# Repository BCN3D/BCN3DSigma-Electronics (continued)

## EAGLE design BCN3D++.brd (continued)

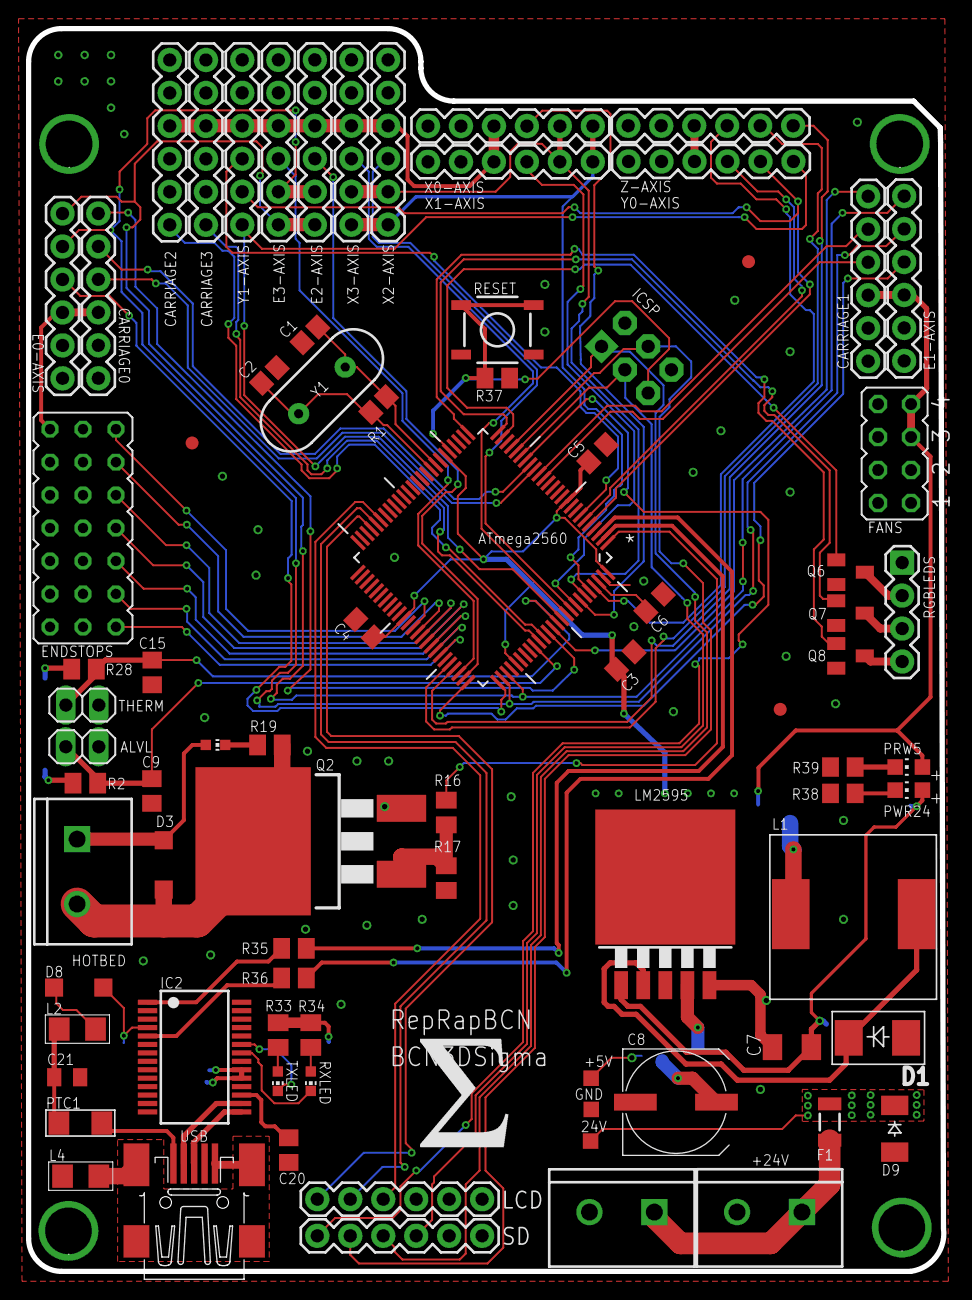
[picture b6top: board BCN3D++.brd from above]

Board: 2 copper layers, 70.5 x 95.8 mm, 87 parts (1 on the bottom side), 79 nets.

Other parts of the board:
U$5: SIGMA_LOGO

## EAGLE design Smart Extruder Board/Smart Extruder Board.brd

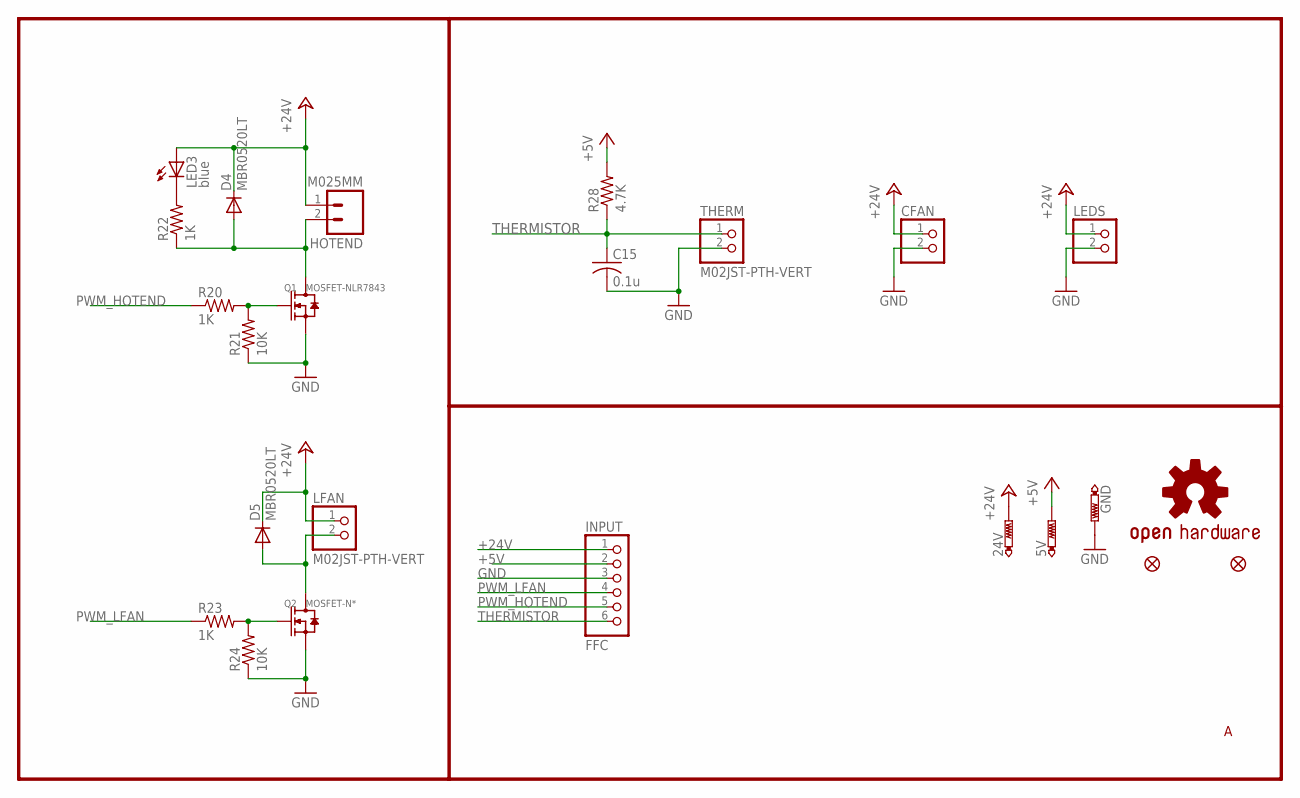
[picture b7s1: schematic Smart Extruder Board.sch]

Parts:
5V, 24V: PTR1TP10SQ; TP10SQ
C15: 0.1u; C0805; MPN 08055C104KAT2A
CFAN: PINHD-1X2/90; 1X02/90
D4, D5: MBR0520LT; SOD123; MPN B0530W-7-F
GND: PTR1TP10SQ; TP10SQ
HOTEND: M025MM; SCREWTERMINAL-5MM-2
INPUT: FFC; 1X06/90
JP1, JP3: SPARKFUN_FIDUCIAL1X2.5; SPARKFUN_FIDUCIAL-1X2.5
LED3: blue; CHIP-LED0805; MPN OVS-0803
LEDS: PINHD-1X2/90; 1X02/90
LFAN: M02JST-PTH-VERT; 1X02/90
LOGO1: OSHW-LOGOS; OSHW-LOGO-S
Q1: MOSFET-NLR7843; TO252; MPN IRLR7843PBF
Q2: MOSFET-N*; SOT23; MPN IRLML6344TRPBF
R20, R22, R23: 1K; M0805; MPN CR0805-JW-102ELF
R21, R24: 10K; M0805; MPN CR0805-JW-103ELF
R28: 4.7K; M0805; MPN CR0805-FX-4701GLF
THERM: M02JST-PTH-VERT; 1X02/90

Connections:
+5V: 5V.TP, INPUT.2, R28.2
+24V: 24V.TP, CFAN.1, D4.C, D5.C, HOTEND.1, INPUT.1, LED3.A, LEDS.1, LFAN.1
GND: C15.2, CFAN.2, GND.TP, INPUT.3, LEDS.2, Q1.2 (S), Q2.2 (S), R21.1, R24.1, THERM.2
unnamed: Q1.1 (G), R20.2, R21.2
unnamed: D4.A, HOTEND.2, Q1.3 (D), R22.1
unnamed: LED3.C, R22.2
unnamed: Q2.1 (G), R23.2, R24.2
unnamed: D5.A, LFAN.2, Q2.3 (D)
PWM_HOTEND: INPUT.5, R20.1
PWM_LFAN: INPUT.4, R23.1
THERMISTOR: C15.1, INPUT.6, R28.1, THERM.1

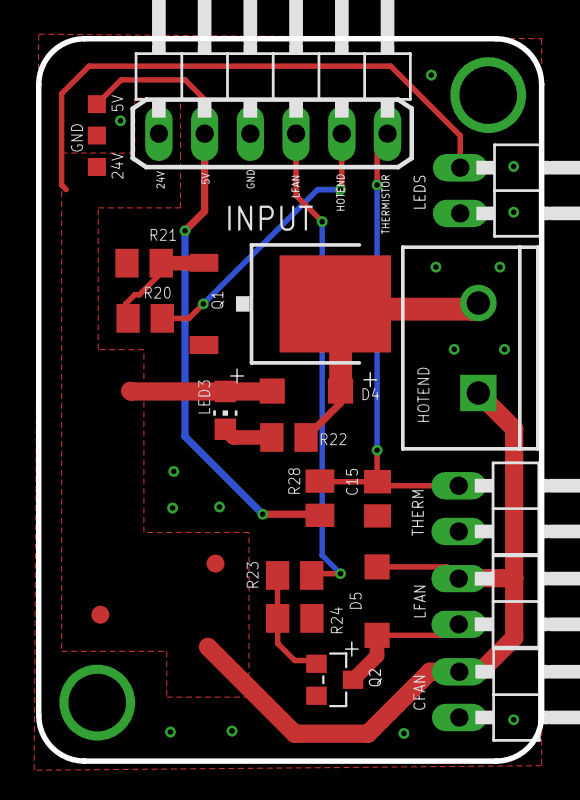
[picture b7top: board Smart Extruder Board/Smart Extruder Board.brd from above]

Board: 2 copper layers, 27.9 x 40.1 mm, 25 parts (1 on the bottom side), 11 nets.

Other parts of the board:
DRILEGEND: DRILEGEND

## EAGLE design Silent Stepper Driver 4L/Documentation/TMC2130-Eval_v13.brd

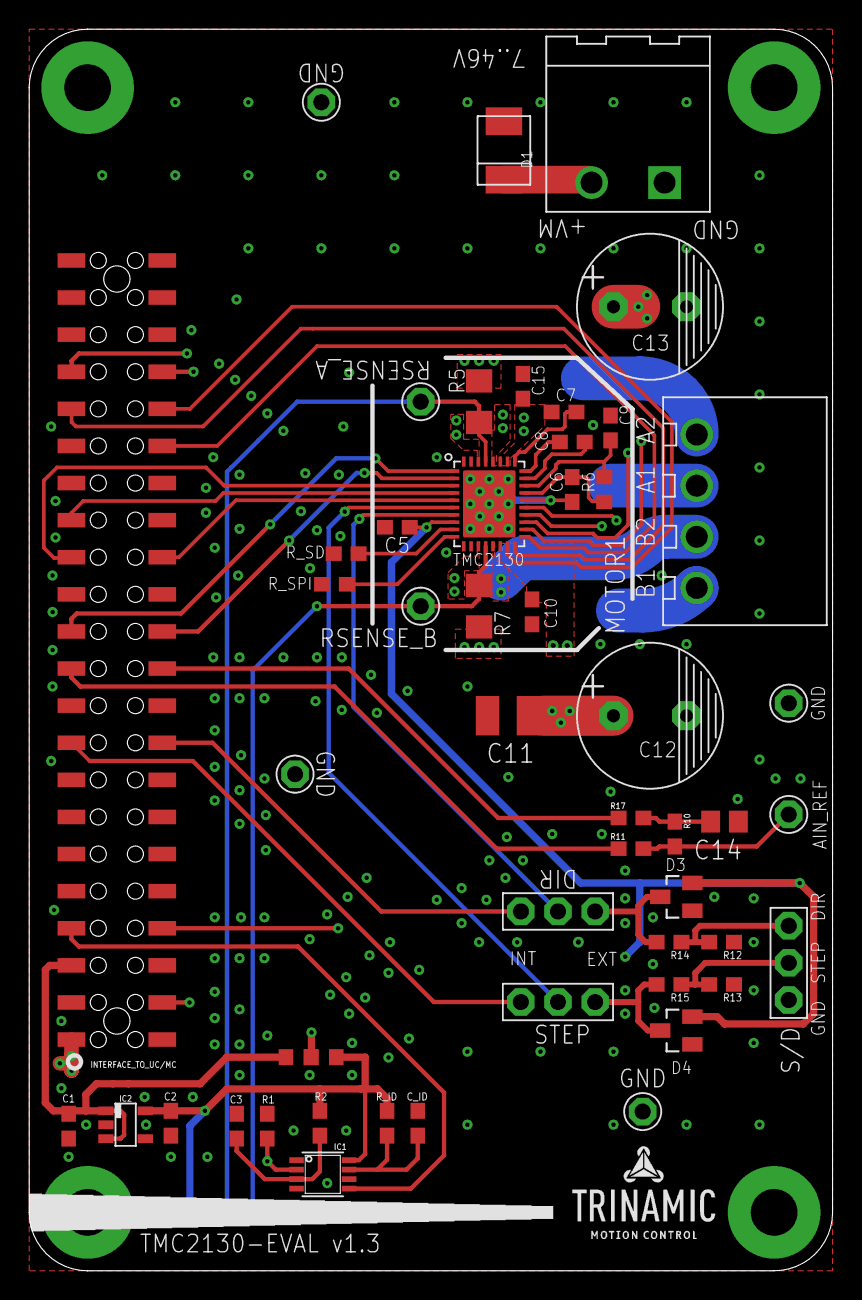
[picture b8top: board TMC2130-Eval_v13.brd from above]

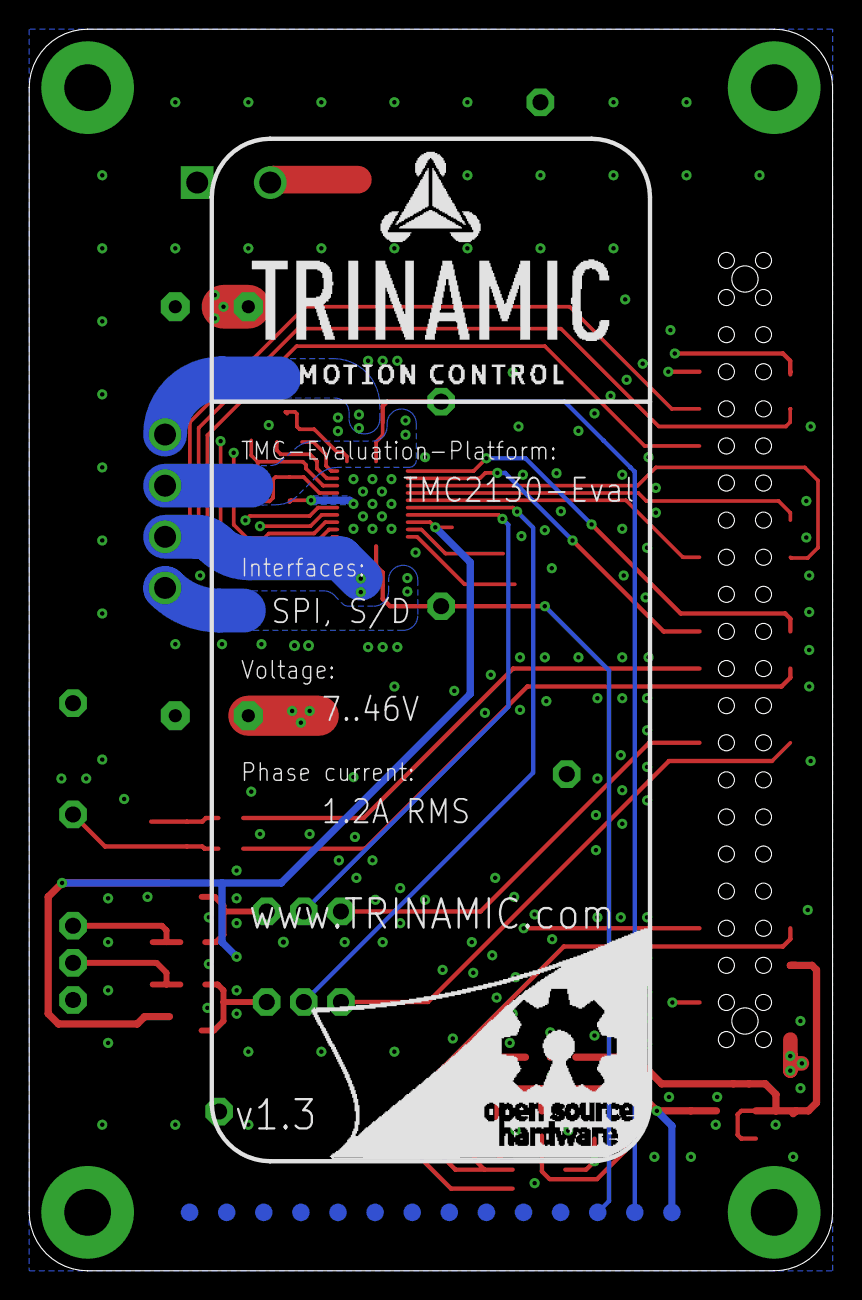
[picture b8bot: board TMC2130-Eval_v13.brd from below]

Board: 4 copper layers, 55.0 x 85.0 mm, 71 parts (15 on the bottom side), 45 nets.

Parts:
AIN_REF: NOT ASSEMBLED; 1PIN_1ROW_THT
C1, C2: 0603/4.7µF/10V; RCL_0603
C3: 0603/10nF/10V; RCL_0603
C5, C7, C10, C15: C0603/100nF/50V; C0603
C6: C0603/4µ7/16V; C0603
C8: C0603/22nF/50V; C0603
C9: C0603/470nF/16V; C0603
C11: 1210/4.7uF/100V; C1210
C12, C13: EEUFR1J151 150uF/63V/0R045; C_POL_RAD_THT_5X10X12.5
C14: 0805/4µ7/50V; C0805
C_ID: C_ID/10V/1%; RCL_0603
D1: SMBJ43A; SMB
D3, D4: BAT54S; SOT23
IC1: SN74LVC1G123DCTR
IC2: LP2985AIM5-3.3; SOT23-5
INTERFACE_TO_UC/MC: FEMALE_HEADER_SMD_254_44_PIN_SHORTPADS_HOLES
JMP1: JUMPER_2.54MM BLACK ON X2; EXTRA_TERMINAL
JMP2: JUMPER_2.54MM BLACK ON X1; EXTRA_TERMINAL
MOTOR1: AKL182_04_POL_HEADER; AKL169_04_POL
PROBE_GND, PROBE_GND1, PROBE_GND2, PROBE_GND3: NOT ASSEMBLED; 1PIN_1ROW_THT
PWR: AKL_349_02_POL_HEADER; AKL349_02_POL
R1: 0603/10k/1%; RCL_0603
R2: 10K; RCL_0603
R5, R7: R1206,0R22/0.5W; R1206
R6: 0603/2R2/1%; R0603
R8: NOT ASSEMBLED; R0603
R9: 0603/0R; R0603
R10: 10k/0603/1%; RCL_0603
R11: 15k/0603/1%; RCL_0603
R12, R13: 0603/10k/1%; 0603
R14, R15: 0603/1k/1%; 0603
R17: 4k7/0603/1%; RCL_0603
REF2: MALE HEADER 2.54; 3PIN_1ROW_2,54_THT
RSENSE_A: NOT ASSEMBLED; 1PIN_1ROW_THT
RSENSE_B: NOT ASSEMBLED; 1PIN_1ROW_THT
R_ID: R_ID/1%; RCL_0603
R_SD: NOT_ASSEMBLED; RCL_0603
R_SPI: NOT_ASSEMBLED; RCL_0603
TERM1: AKL_330_2_POL_TERMINAL; EXTRA_TERMINAL
TERM2: AKL182_04_POL_TERMINAL; EXTRA_TERMINAL
TEST_POINT1, TEST_POINT2, TEST_POINT3, TEST_POINT4, TEST_POINT5, TEST_POINT6, TEST_POINT7, TEST_POINT8, TEST_POINT9, TEST_POINT10, TEST_POINT11, TEST_POINT12, TEST_POINT13, TEST_POINT14: NOT ASSEMBLED; PAD_R1.2
TMC2130: TMC2130_QFN36; QFN36
U$1: TMC_EVAL_RIGHT_BAR
U$3: TMC_EVAL_BACK_NO_DOCU
X1, X2: MALE HEADER 2.54; 3PIN_1ROW_2,54_THT

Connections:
+3V3: C2.1, IC1.8, IC2.5, R2.1, R9.1, R_ID.2, TEST_POINT1.P$1
+5V_USB: C1.1, IC2.1, IC2.3, INTERFACE_TO_UC/MC.5, R8.2
AIN_REF: AIN_REF.1, R10.2, R11.2, TMC2130.23
AIN_REF_PWM: INTERFACE_TO_UC/MC.22, R17.1
AIN_REF_SW: INTERFACE_TO_UC/MC.21, R11.1
CLK: INTERFACE_TO_UC/MC.23, TMC2130.1
CSN_CFG3: INTERFACE_TO_UC/MC.24, TMC2130.2
DRV_ENN_CFG6: INTERFACE_TO_UC/MC.8, TMC2130.22
ENCA_DCIN_CFG5: INTERFACE_TO_UC/MC.34, TMC2130.19
ENCB_DCEN_CFG4: INTERFACE_TO_UC/MC.35, TMC2130.18
ENCN_DCO: INTERFACE_TO_UC/MC.36, TMC2130.17
EXT_DIR: D3.3, R14.2, X2.1
EXT_DIR_CON: R12.2, R14.1, REF2.1
EXT_STEP: D4.3, R15.2, X1.1
EXT_STEP_CON: R13.2, R15.1, REF2.2
GND: C1.2, C2.2, C3.2, C5.2, C6.2, C9.1, C10.1, C11.2, C12.-, C13.-, C14.1, C15.1, C_ID.2, D1.A, D3.1, D4.1, IC1.1, IC1.4, IC1.6, IC2.2, INTERFACE_TO_UC/MC.2, INTERFACE_TO_UC/MC.3, INTERFACE_TO_UC/MC.43, INTERFACE_TO_UC/MC.44, PROBE_GND.1, PROBE_GND1.1, PROBE_GND2.1, PROBE_GND3.1, PWR.1, R1.2, R5.1, R7.1, R12.1, R13.1, REF2.3, R_SD.1, R_SPI.1, TEST_POINT14.P$1, TMC2130.11, TMC2130.12, TMC2130.24, TMC2130.35, TMC2130.36, TMC2130.GND_PAD
ID_CH1: IC1.5, INTERFACE_TO_UC/MC.7
ID_CLK: IC1.2, INTERFACE_TO_UC/MC.4, R1.1
INT_DIR: INTERFACE_TO_UC/MC.18, X2.3
INT_STEP: INTERFACE_TO_UC/MC.17, X1.3
M1A: MOTOR1.3, TMC2130.34
M1A2: MOTOR1.4, TMC2130.32
M1B1: MOTOR1.1, TMC2130.13
M1B2: MOTOR1.2, TMC2130.15
unnamed: C3.1, IC1.3, R2.2
unnamed: C_ID.1, IC1.7, R_ID.1
unnamed: R_SPI.2, TMC2130.10
unnamed: R_SD.2, TMC2130.9
unnamed: C6.1, R6.1, TMC2130.25
unnamed: C8.1, TMC2130.28
unnamed: C8.2, TMC2130.27
unnamed: C7.2, TMC2130.29
unnamed: C9.2, R6.2, TMC2130.26
unnamed: C14.2, R10.1, R17.2
SCK_CFG2: INTERFACE_TO_UC/MC.27, TMC2130.3
SDI_NAI_CFG1: INTERFACE_TO_UC/MC.29, TMC2130.4
SDO_NAO_CFG0: INTERFACE_TO_UC/MC.28, TMC2130.5
SENSEA: R5.2, RSENSE_A.1, TEST_POINT2.P$1, TMC2130.33
SENSEB: R7.2, RSENSE_B.1, TEST_POINT3.P$1, TMC2130.14
SEP_DIAG1: INTERFACE_TO_UC/MC.38, TMC2130.21
SWN_DIAG0: INTERFACE_TO_UC/MC.37, TMC2130.20
VCC_IO: C5.1, D3.2, D4.2, R8.1, R9.2, TMC2130.8
VM: C7.1, C10.2, C11.1, C12.+, C13.+, C15.2, D1.C, INTERFACE_TO_UC/MC.1, PWR.2, TMC2130.16, TMC2130.30, TMC2130.31
[REFL]_STEP: TMC2130.6, X1.2
[REFR]_DIR: TMC2130.7, X2.2

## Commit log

2014-11-21 Adding the first files to git.This is the revision A of the boards
2014-11-21 Main Board almost ready
    5V rail to ICSP and some headers left to connect
2014-11-25 New File Tree and Updates
2014-11-27 Just git ignore and gitattributes
2014-12-24 Updates!
    Rev_A Ready and firsts prototypes
2014-12-29 Updated files
2015-02-13 The new REV_B has been shipped to production
    New MainBoard Design, new Stepper drivers and new Extruder Board.
    We also added many new components and configurations
2016-04-08 BCN3D Electronics REV.E tested and manufactured
2016-04-29 Updated README
    new sections
2016-04-29 gitignore
2016-05-04 CERN OHL Added!
    Also updated the README doc
2016-05-04 typos
2016-05-11 Fixed thermistor series resistors
    Added new license info and WEEE/FCC/CE Logo.
2016-09-27 Extruder board REV. F now on production
    New Extruder Board design for the late 2016 BCN3D Sigma 3D Printer
2016-09-27 Silent Stepper Driver TMC2130 based REV.B
    2 Layer board for the TMC2130 based Stepper Driver board
2016-10-24 Update Ignore File and delete Eagle Lock files
2016-10-28 Added img folder for the wiki
2016-11-02 Add GIFS for the wiki
2016-11-02 Motherboard updated to new version REV.G
    Basically the only change in REV.G is the 20 contacts Flat Flexible
    Cable connector.
2017-02-09 File for the REV.H
    Files from the REV.H Released with new and more documentation.
2017-02-09 Added GERBER Files
2017-03-09 Added Gitter badge link
2017-04-11 New SD Reader
    Add first revision files REVA
2017-04-11 update README for the SD Reader
2018-01-18 License upgrade
2021-11-09 Update README.md
    https://forum.kicad.info/t/warning-avoid-all-links-to-kicad-pcb-org-use-kicad-org/31521
